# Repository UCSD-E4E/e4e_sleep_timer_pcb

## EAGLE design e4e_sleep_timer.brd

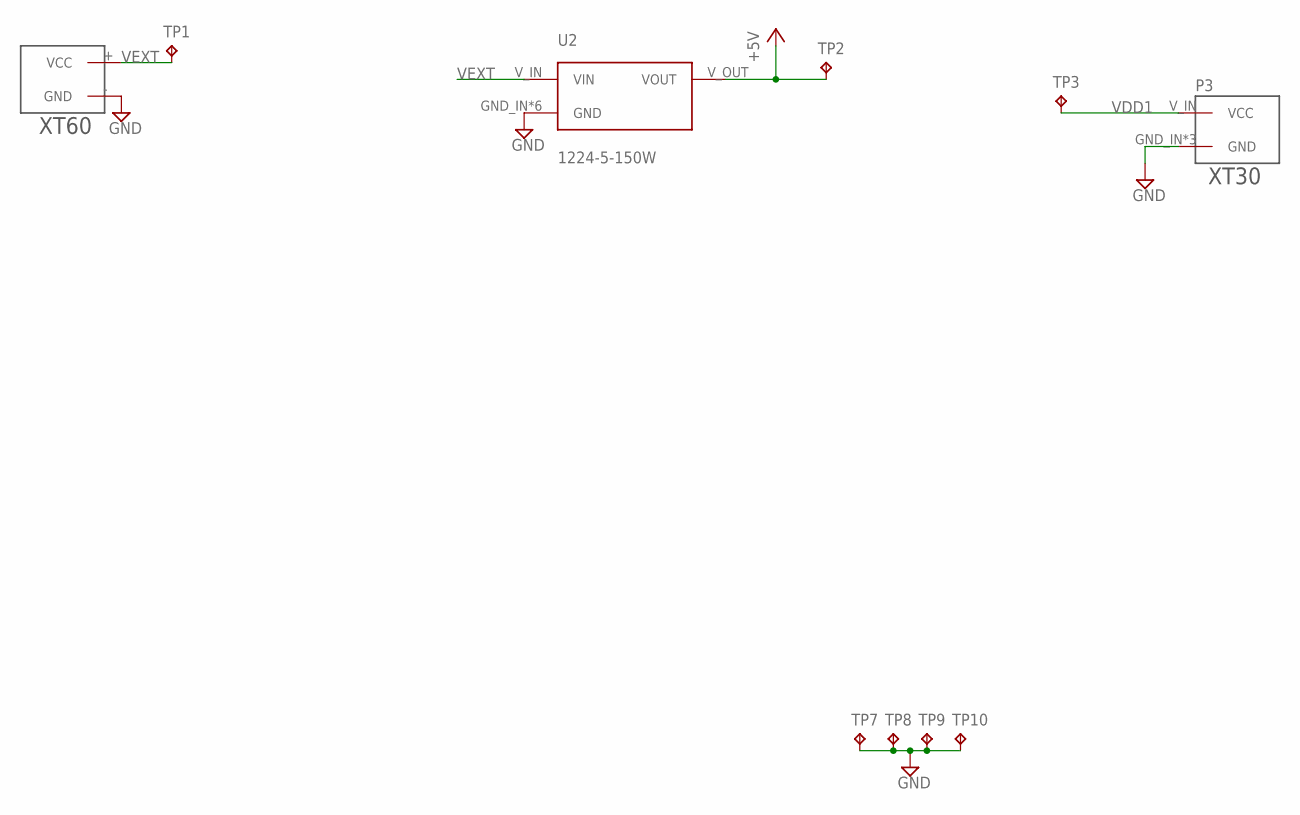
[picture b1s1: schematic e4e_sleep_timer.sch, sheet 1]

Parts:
P1: XT60
P3: XT30PW-F
TP1, TP2, TP3, TP7, TP8, TP9, TP10: TPPAD1-13; P1-13
U2: 1224-5-150W; 2X_XT30

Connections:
+5V: TP2.TP, U2.V_OUT (VOUT); also elsewhere on the board
GND: P1.- (GND), P3.GND_IN (GND), P3.S1 (GND), P3.S2 (GND), TP7.TP, TP8.TP, TP9.TP, TP10.TP, U2.GND_IN (GND), U2.GND_OUT (GND), U2.S1 (GND), U2.S2 (GND), U2.S3 (GND), U2.S4 (GND); also elsewhere on the board
VDD1: P3.V_IN (VCC), TP3.TP; also elsewhere on the board
VEXT: P1.+ (VCC), TP1.TP, U2.V_IN (VIN)

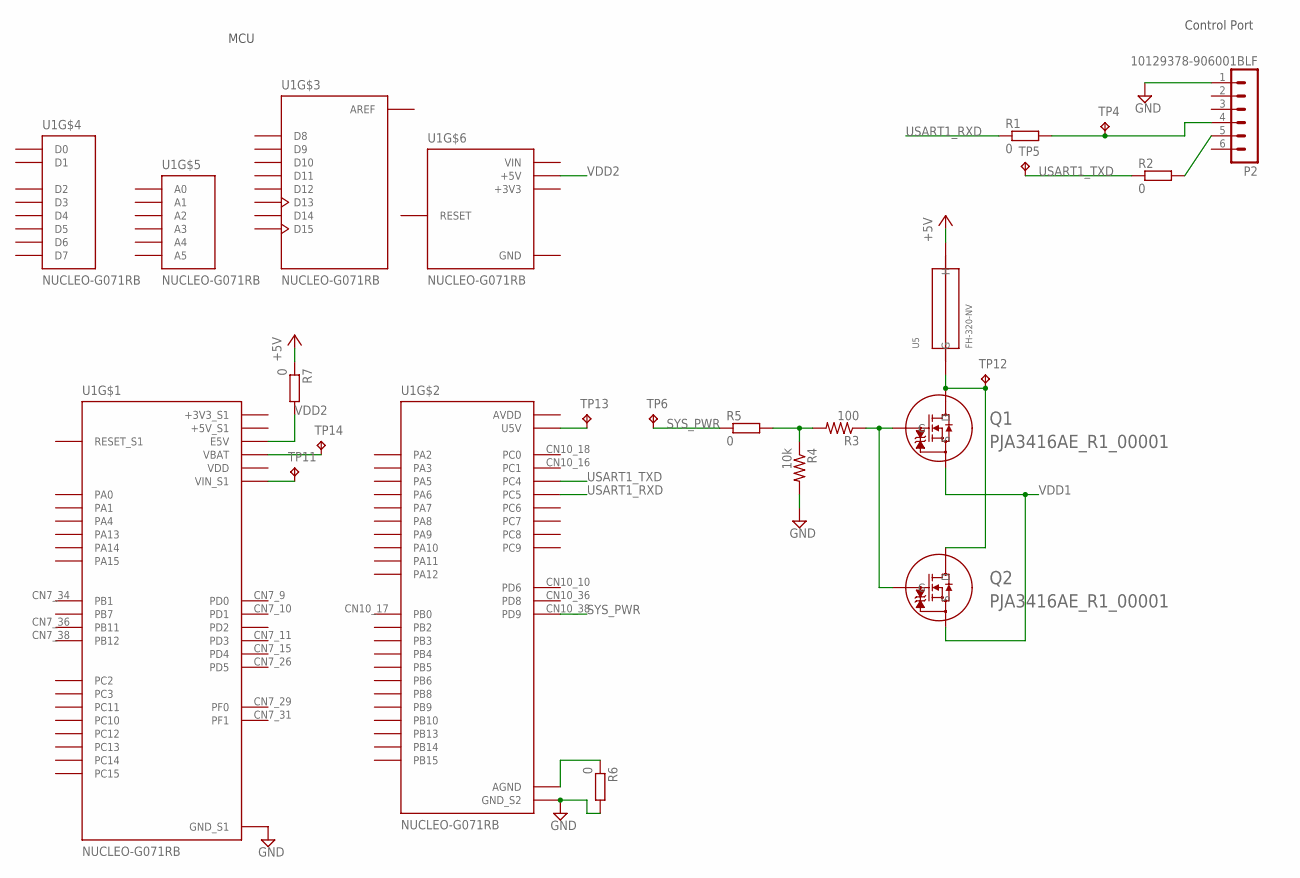
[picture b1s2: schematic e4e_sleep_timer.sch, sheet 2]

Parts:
P2: 10129378-906001BLF; MA06-1
Q1, Q2: PJA3416AE_R1_00001; SOT23_PJA3416_PNJ
R1, R2, R5, R6, R7: 0; R0603
R3: 100; R0603
R4: 10k; R0603
TP4, TP5, TP6: TPPAD1-13; P1-13
TP11, TP12, TP13, TP14: TPTP20R; TP20R
U1: NUCLEO-G071RB; ST_NUCLEO-64
U5: FH-320-NV

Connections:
+3V3: U1.CN6_2 (+3V3), U1.CN6_4 (+3V3)
+3V3_S1: U1.CN7_12 (+3V3_S1), U1.CN7_16 (+3V3_S1)
+5V: R7.1, U5.2 (H); also elsewhere on the board
+5V_S1: U1.CN7_18 (+5V_S1)
AREF: U1.CN5_8 (AREF)
AVDD: U1.CN10_7 (AVDD)
GND: P2.1, R4.2, R6.2, U1.CN6_6 (GND), U1.CN6_7 (GND), U1.CN7_8 (GND_S1), U1.CN7_19 (GND_S1), U1.CN7_20 (GND_S1), U1.CN7_22 (GND_S1), U1.CN10_20 (GND_S2); also elsewhere on the board
unnamed: P2.4, R1.2, TP4.TP
unnamed: Q1.1 (G), Q2.1 (G), R3.1
unnamed: P2.5, R2.2
unnamed: R3.2, R4.1, R5.2
unnamed: Q1.3 (D), Q2.3 (D), TP12.TP, U5.1 (G)
unnamed: TP11.TP, U1.CN7_24 (VIN_S1)
unnamed: R6.1, U1.CN10_9 (AGND), U1.CN10_32 (AGND)
unnamed: TP13.TP, U1.CN10_8 (U5V)
unnamed: TP14.TP, U1.CN7_33 (VBAT)
SYS_PWR: R5.1, TP6.TP, U1.CN10_38 (PD9)
USART1_RXD: R1.1, U1.CN10_37 (PC5)
USART1_TXD: R2.1, TP5.TP, U1.CN10_35 (PC4)
VDD: U1.CN7_5 (VDD)
VDD1: Q1.2 (S), Q2.2 (S); also elsewhere on the board
VDD2: R7.2, U1.CN6_5 (+5V), U1.CN7_6 (E5V)
VIN: U1.CN6_1 (VIN)

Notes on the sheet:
Control Port
MCU

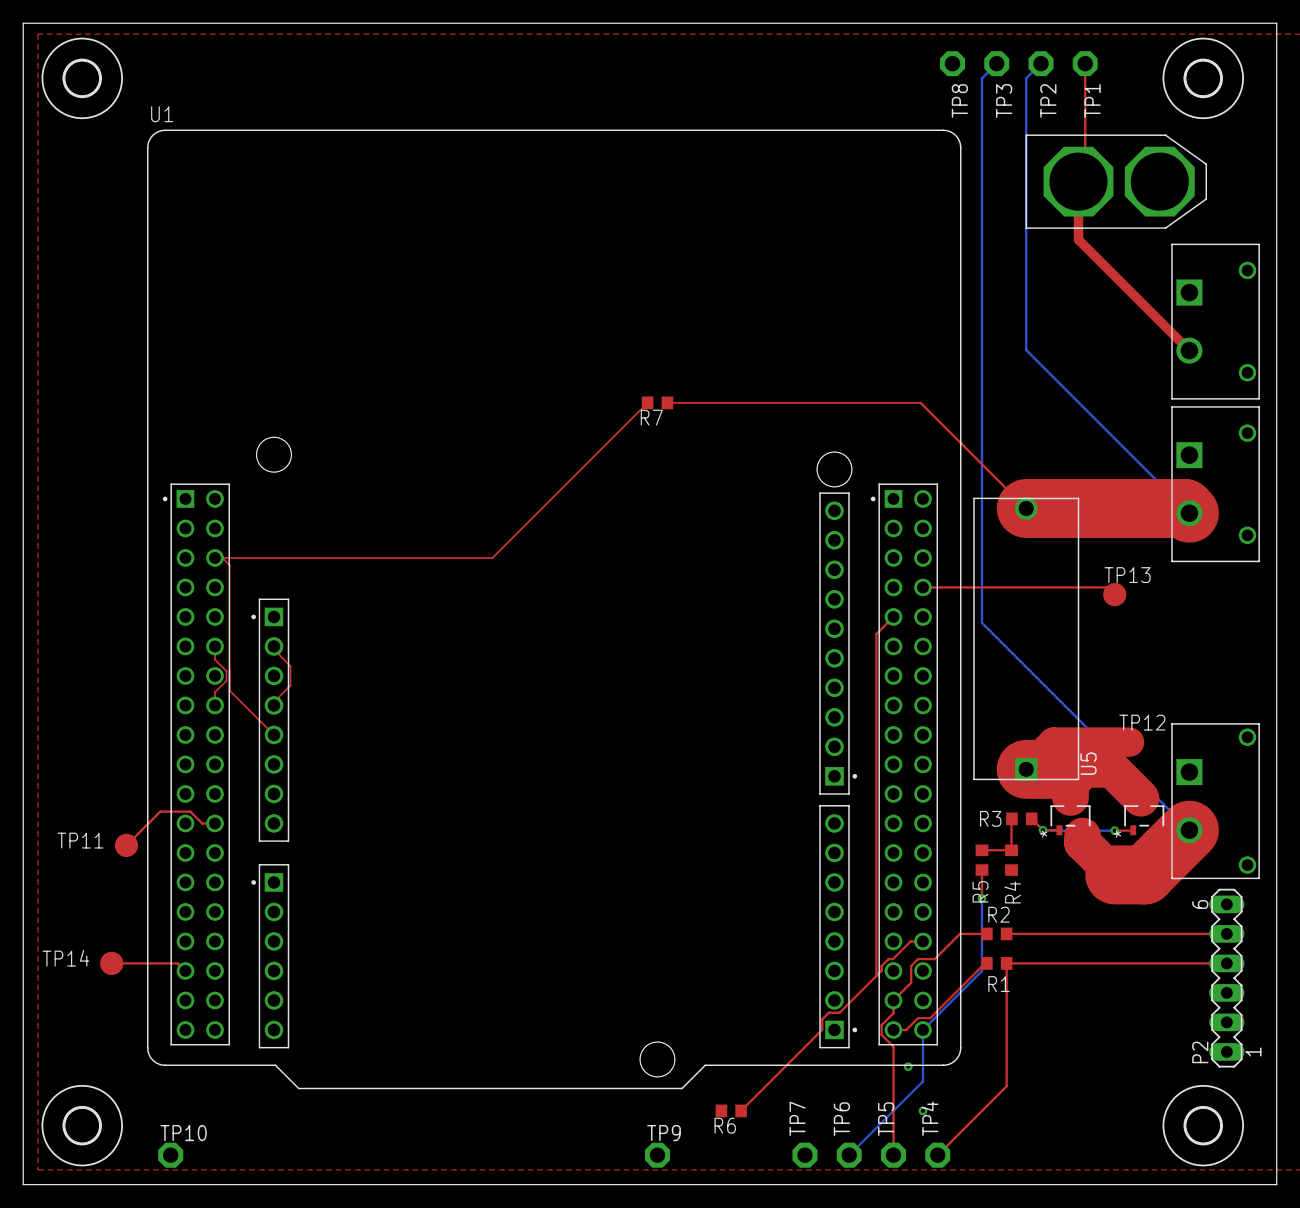
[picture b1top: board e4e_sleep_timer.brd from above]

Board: 2 copper layers, 107.9 x 100.0 mm, 33 parts (0 on the bottom side), 19 nets.

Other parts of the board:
U$1, U$2, U$3, U$4: 3,0

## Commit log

2022-04-29 Adding initial schematic
2022-04-29 Adding interim files
2022-04-29 Adding library files
2022-04-29 Removing backup files
2022-04-29 Added regulator, external power
2022-04-29 Updating project
2022-05-03 Completed PCB design
2022-05-12 Finished PCB review
2022-05-17 Added Nucleo Board power bypass
2023-05-15 Added circuit docs

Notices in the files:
parts and their libraries:
COPYRIGHT: Copyright (C) 2022 Ultra Librarian. All rights reserved.
